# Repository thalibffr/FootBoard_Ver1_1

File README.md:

<html lang="en">
  <head>
    <meta charset="uft-8">
    <meta name="author" content="Thalib Falih Fadhil Rabbani">
  </head>
  <body>
    <h1>ICHIRO Footboard Ver 1.1</h1>
    <p>
      Below is the design of the humanoid robot leg board to optimize the way the robot walks using the loadcell sensor.
      <br>
      <table>
        <tr>
          <td>
            <div align="center">
              3D Top View
            </div>
          </td>
          <td>
            <div align="center">
              3D Bottom View
            </div>
          </td>
          <td>
            <div align="center">
              After mounting components
            </div>
          </td>     
        </tr>
        <tr>
          <td>
            <a href="image/loadcell_v1.1 top.png.jpeg">
              <div align="center">
                
              </div>
            </a>
          </td>
          <td>
            <div align="center">
              
            </div>
          </td>
          <td>
            <div align="center">
              
            </div>
          </td>
        </tr>
      </table>
    </p>
    <h2>Repository Contents</h2>
    <p>
      <ul>
        <li><a href="">Repository Contents</li>
        <li><a href="">Development</a></li>
        <li><a href="">Contact</a></li>
      </ul>
    </p>
    <h2>Development</h2>
    <p>
      <h3>BOM</h3>
    </p>
    <table>
    <tr>
      <td>ID</td>
      <td>Designator</td>
      <td>Footprint</td>
      <td>Quantity</td>
      <td>Supplier</td>
    </tr>
    <tr>
      <td>1</td>
      <td>R4</td>
      <td>R_0805_2012Metric</td>
      <td>1</td>
      <td></td>
    </tr>
    <tr>
      <td>2</td>
      <td>H4,H2,H1,H3</td>
      <td>MountingHole_3mm</td>
      <td>4</td>
      <td></td>
    </tr>
    <tr>
      <td>3</td>
      <td>R12,R11,R13,R2</td>
      <td>R_0805_2012Metric</td>
      <td>4</td>
      <td></td>
    </tr>
    <tr>
      <td>4</td>
      <td>C4,C6,C5</td>
      <td>C_0805_2012Metric</td>
      <td>3</td>
      <td></td>
    </tr>
    <tr>
      <td>5</td>
      <td>J8</td>
      <td>PinHeader_1x01_P2.54mm_Vertical</td>
      <td>1</td>
      <td></td>
    </tr>
    <tr>
      <td>6</td>
      <td>FR,BR,FL,BL</td>
      <td>JST_B4B-PH-K-S(LF)(SN)</td>
      <td>4</td>
      <td></td>
    </tr>
    </table>
    <h2>Contact</h2>
    <p>
      If you have any question feel free to contact <a href="mailto:thalibfalih@gmail.com">thalibfalih@gmail.com</a> to ask it, or open an issue on this repository.
    </p>
  </body>
</html>

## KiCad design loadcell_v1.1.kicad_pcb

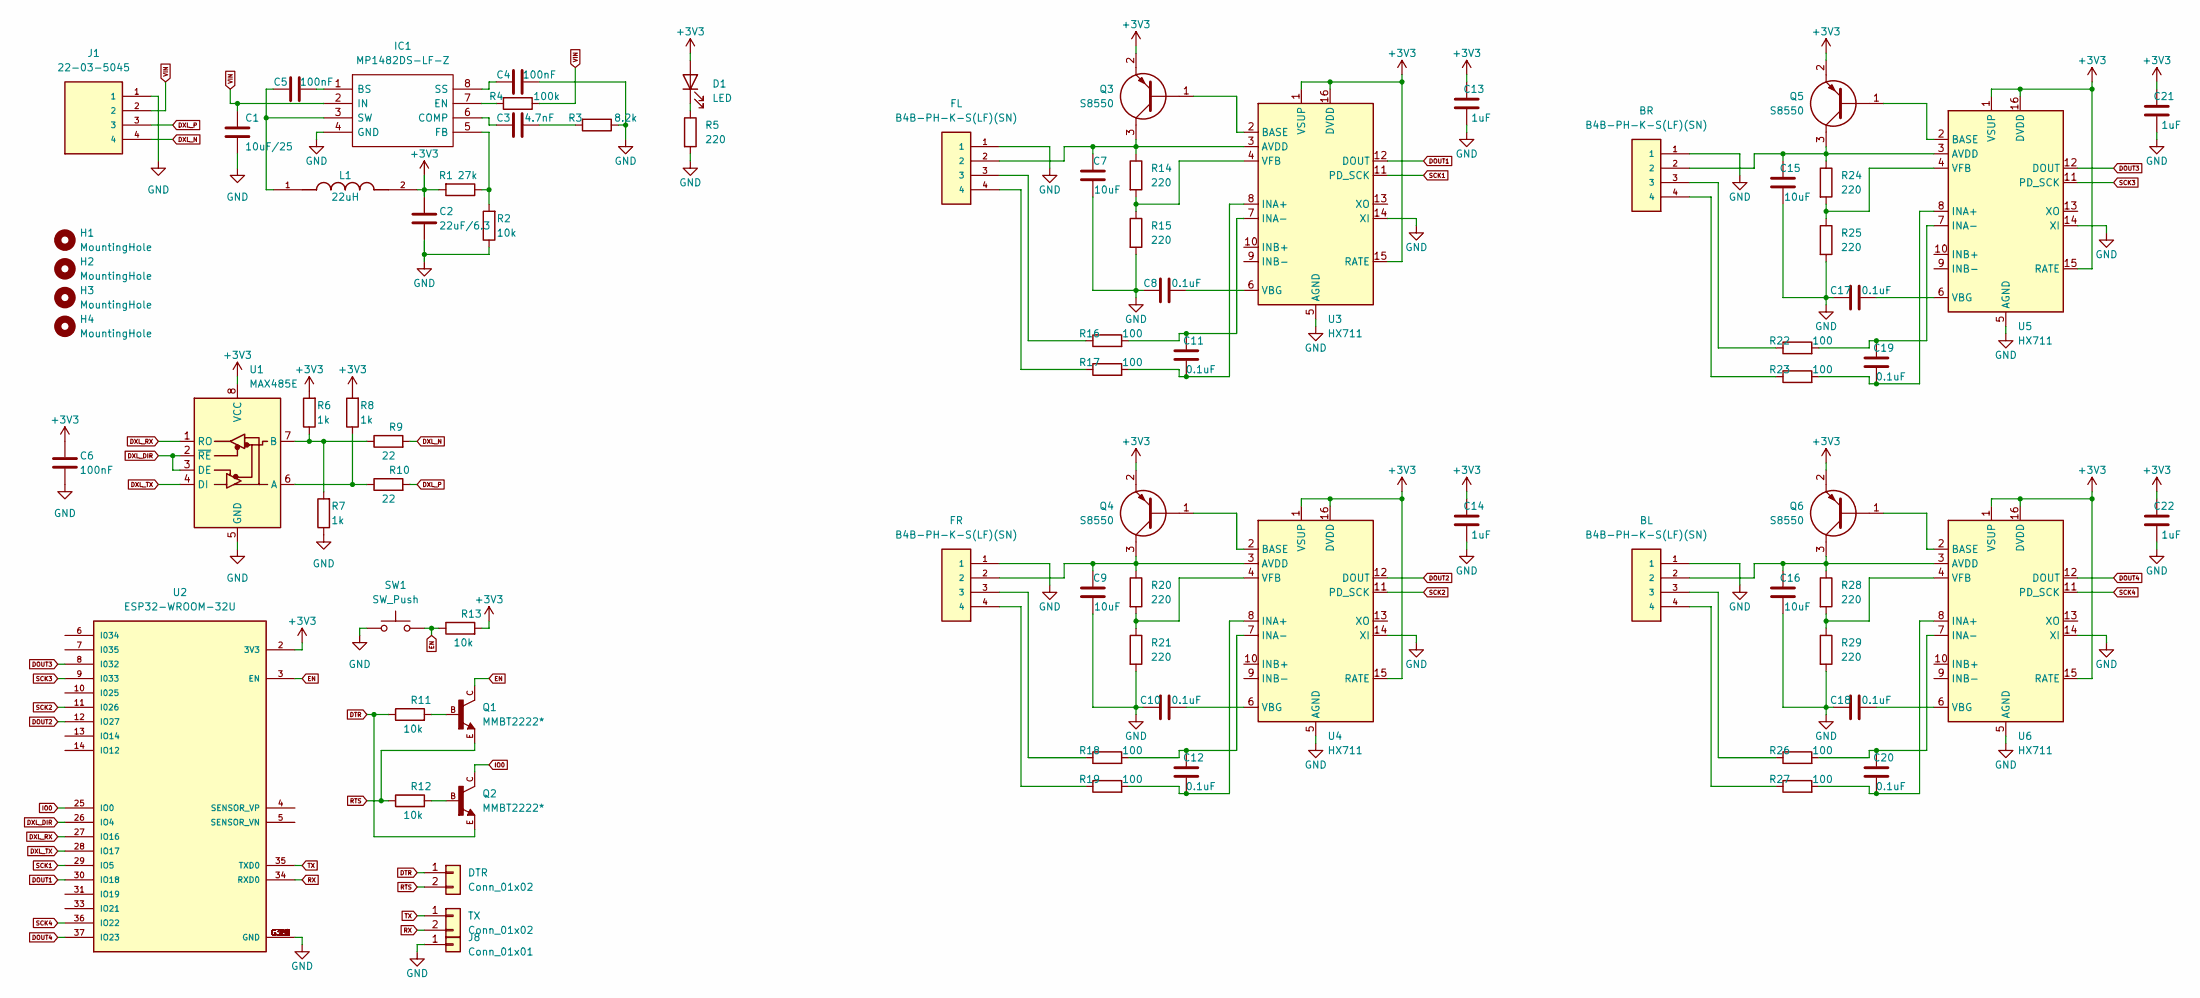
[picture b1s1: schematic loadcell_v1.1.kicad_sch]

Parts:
BL: B4B-PH-K-S(LF)(SN); JST_B4B-PH-K-S(LF)(SN)
BR: B4B-PH-K-S(LF)(SN); JST_B4B-PH-K-S(LF)(SN)
C1: 10uF/25; C_0805_2012Metric
C2: 22uF/6.3; C_0805_2012Metric
C3: 4.7nF; C_0805_2012Metric
C4, C5, C6: 100nF; C_0805_2012Metric
C7, C9, C15, C16: 10uF; C_0805_2012Metric
C8, C10, C11, C12, C17, C18, C19, C20: 0.1uF; C_0805_2012Metric
C13, C14, C21, C22: 1uF; C_0805_2012Metric
D1: LED; LED_0805_2012Metric
DTR: Conn_01x02; PinHeader_1x02_P2.54mm_Vertical
FL: B4B-PH-K-S(LF)(SN); JST_B4B-PH-K-S(LF)(SN)
FR: B4B-PH-K-S(LF)(SN); JST_B4B-PH-K-S(LF)(SN)
H1, H2, H3, H4: MountingHole; MountingHole_3mm
IC1: MP1482DS-LF-Z; SOIC127P600X175-8N; Manufacturer_Part_Number MP1482DS-LF-Z; Mouser Part Number 946-MP1482DSLFZ
J1: 22-03-5045; MOLEX_22-03-5045; PARTREV B
J8: Conn_01x01; PinHeader_1x01_P2.54mm_Vertical
L1: 22uH; IND_VLS6045EX-3R3N; PARTREV N/A
Q1, Q2: MMBT2222*; SOT23-BEC
Q3, Q4, Q5, Q6: S8550; SOT95P240X115-3N; Manufacturer_Part_Number S8550
R1: 27k; R_0805_2012Metric
R2, R11, R12, R13: 10k; R_0805_2012Metric
R3: 8.2k; R_0805_2012Metric
R4: 100k; R_0805_2012Metric
R5, R14, R15, R20, R21, R24, R25, R28, R29: 220; R_0805_2012Metric
R6, R7, R8: 1k; R_0805_2012Metric
R9, R10: 22; R_0805_2012Metric
R16, R17, R18, R19, R22, R23, R26, R27: 100; R_0805_2012Metric
SW1: SW_Push; SW_SPST_CK_RS282G05A3
TX: Conn_01x02; PinHeader_1x02_P2.54mm_Vertical
U1: MAX485E; SOIC127P600X175-8N
U2: ESP32-WROOM-32U; XCVR_ESP32-WROOM-32U; PARTREV V1.9
U3, U4, U5, U6: HX711; SOP127P600X180-16N

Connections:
+3V3: C2.2, C6.2, C13.2, C14.2, C21.2, C22.2, D1.2 (A), L1.2, Q3.2, Q4.2, Q5.2, Q6.2, R1.2, R6.2, R8.2, R13.2, U1.8 (VCC), U2.2 (3V3), U3.1 (VSUP), U3.15 (RATE), U3.16 (DVDD), U4.1 (VSUP), U4.15 (RATE), U4.16 (DVDD), U5.1 (VSUP), U5.15 (RATE), U5.16 (DVDD), U6.1 (VSUP), U6.15 (RATE), U6.16 (DVDD)
DOUT1: U2.30 (IO18), U3.12 (DOUT)
DOUT2: U2.12 (IO27), U4.12 (DOUT)
DOUT3: U2.8 (I032), U5.12 (DOUT)
DOUT4: U2.37 (IO23), U6.12 (DOUT)
DTR: DTR.1, Q2.E, R11.1
DXL_DIR: U1.2 (~RE), U1.3 (DE), U2.26 (IO4)
DXL_N: J1.4, R9.2
DXL_P: J1.3, R10.2
DXL_RX: U1.1 (RO), U2.27 (IO16)
DXL_TX: U1.4 (DI), U2.28 (IO17)
EN: Q1.C, R13.1, SW1.2, U2.3 (EN)
GND: BL.1, BR.1, C1.2, C2.1, C4.1, C6.1, C7.1, C8.2, C9.1, C10.2, C13.1, C14.1, C15.1, C16.1, C17.2, C18.2, C21.1, C22.1, FL.1, FR.1, IC1.4 (GND), J1.1, J8.1, R2.1, R3.1, R5.2, R7.1, R15.2, R21.2, R25.2, R29.2, SW1.1, U1.5 (GND), U2.1 (GND), U2.38 (GND), U2.G.11 (GND), U2.G.12 (GND), U2.G.13 (GND), U2.G.14 (GND), U2.G.15 (GND), U2.G.16 (GND), U2.G.17 (GND), U2.G.18 (GND), U2.G.19 (GND), U2.G.20 (GND), U2.G.21 (GND), U2.G.22 (GND), U3.5 (AGND), U3.14 (XI), U4.5 (AGND), U4.14 (XI), U5.5 (AGND), U5.14 (XI), U6.5 (AGND), U6.14 (XI)
IO0: Q2.C, U2.25 (IO0)
unnamed: C3.1, R3.2
unnamed: C3.2, IC1.6 (COMP)
unnamed: C4.2, IC1.8 (SS)
unnamed: C5.1, IC1.1 (BS)
unnamed: C5.2, IC1.3 (SW), L1.1
unnamed: C7.2, FL.2, Q3.3, R14.1, U3.3 (AVDD)
unnamed: C8.1, U3.6 (VBG)
unnamed: C9.2, FR.2, Q4.3, R20.1, U4.3 (AVDD)
unnamed: C10.1, U4.6 (VBG)
unnamed: C11.1, R17.2, U3.8 (INA+)
unnamed: C11.2, R16.2, U3.7 (INA-)
unnamed: C12.1, R19.2, U4.8 (INA+)
unnamed: C12.2, R18.2, U4.7 (INA-)
unnamed: BR.2, C15.2, Q5.3, R24.1, U5.3 (AVDD)
unnamed: BL.2, C16.2, Q6.3, R28.1, U6.3 (AVDD)
unnamed: C17.1, U5.6 (VBG)
unnamed: C18.1, U6.6 (VBG)
unnamed: C19.1, R23.2, U5.8 (INA+)
unnamed: C19.2, R22.2, U5.7 (INA-)
unnamed: C20.1, R27.2, U6.8 (INA+)
unnamed: C20.2, R26.2, U6.7 (INA-)
unnamed: D1.1 (K), R5.1
unnamed: IC1.5 (FB), R1.1, R2.2
unnamed: IC1.7 (EN), R4.2
unnamed: FL.3, R16.1
unnamed: FL.4, R17.1
unnamed: FR.3, R18.1
unnamed: FR.4, R19.1
unnamed: BR.3, R22.1
unnamed: BR.4, R23.1
unnamed: BL.3, R26.1
unnamed: BL.4, R27.1
unnamed: Q1.B, R11.2
unnamed: Q2.B, R12.2
unnamed: Q3.1, U3.2 (BASE)
unnamed: Q4.1, U4.2 (BASE)
unnamed: Q5.1, U5.2 (BASE)
unnamed: Q6.1, U6.2 (BASE)
unnamed: R6.1, R7.2, R9.1, U1.7 (B)
unnamed: R8.1, R10.1, U1.6 (A)
unnamed: R14.2, R15.1, U3.4 (VFB)
unnamed: R20.2, R21.1, U4.4 (VFB)
unnamed: R24.2, R25.1, U5.4 (VFB)
unnamed: R28.2, R29.1, U6.4 (VFB)
RTS: DTR.2, Q1.E, R12.1
RX: TX.2, U2.34 (RXD0)
SCK1: U2.29 (IO5), U3.11 (PD_SCK)
SCK2: U2.11 (I026), U4.11 (PD_SCK)
SCK3: U2.9 (I033), U5.11 (PD_SCK)
SCK4: U2.36 (IO22), U6.11 (PD_SCK)
TX: TX.1, U2.35 (TXD0)
VIN: C1.1, IC1.2 (IN), J1.2, R4.1

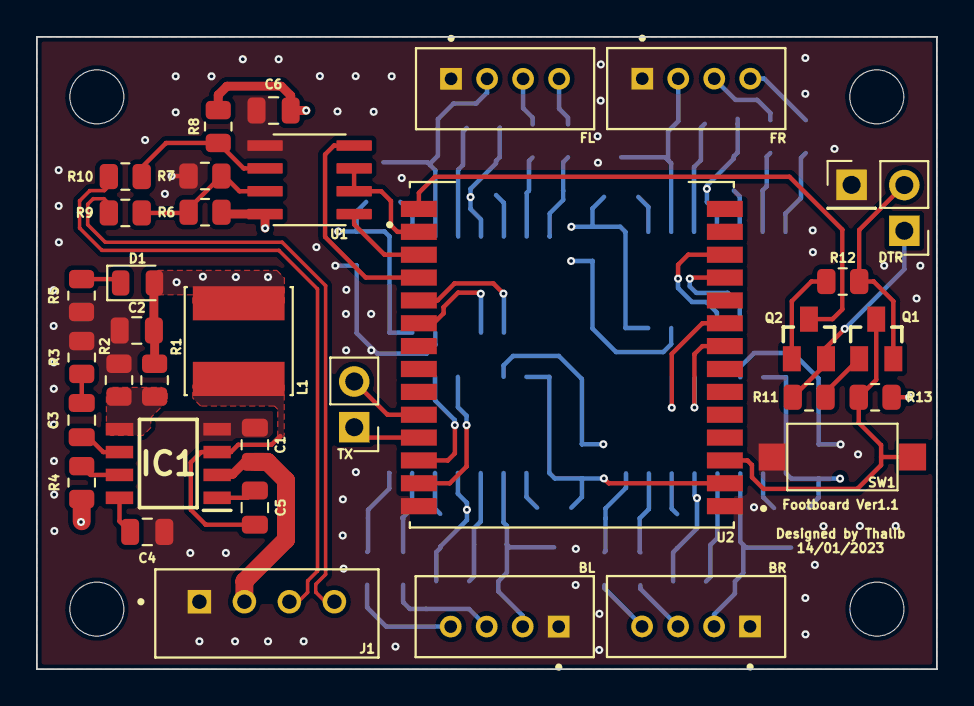
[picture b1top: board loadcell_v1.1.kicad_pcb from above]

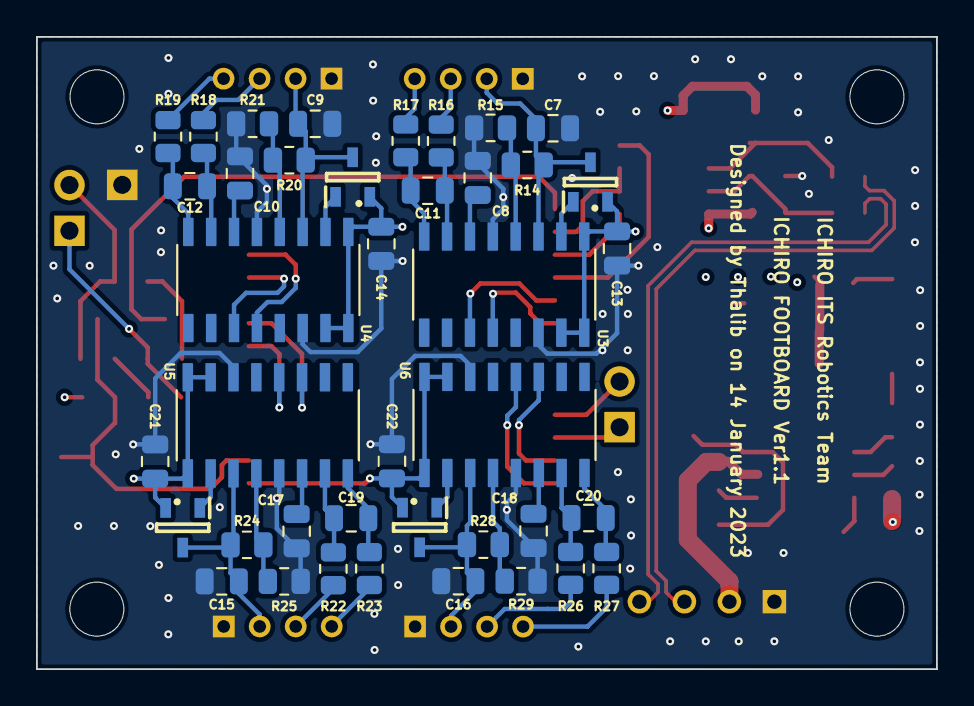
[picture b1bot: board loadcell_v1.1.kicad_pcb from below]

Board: 4 copper layers, 50.0 x 35.1 mm, 79 parts (40 on the bottom side), 66 nets.

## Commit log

2023-02-02 add sch & brd file
2023-05-13 add image file
2023-05-13 add 3d image
2023-05-14 add dummy firmware
2023-10-26 Update README.md BOM
